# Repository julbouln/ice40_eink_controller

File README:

FPGA & STM32F0 driven EINK controller

- Final FPGA board: https://oshpark.com/shared_projects/rBoQ8bop
- The links on the Kitnic page make ordering the parts easier: https://kitnic.it/boards/github.com/julbouln/ice40_eink_controller/
- ifusb companion: https://github.com/julbouln/ifusb

Prototype:
- OLIMEX iCE40HX1K-EVB (https://www.olimex.com/Products/FPGA/iCE40/iCE40HX1K-EVB/open-source-hardware)
- NUCLEO-F042K6 (http://www.st.com/content/st_com/en/products/evaluation-tools/product-evaluation-tools/mcu-eval-tools/stm32-mcu-eval-tools/stm32-mcu-nucleo/nucleo-f042k6.html)
- TPS65185EVM (http://www.ti.com/tool/tps65185evm)
- ED060SC7 Kindle 3 EINK screen (http://www.ebay.com/sch/i.html?_from=R40&_trksid=m570.l1313&_nkw=ED060SC7&_sacat=0)
- custom EINK connector board (https://oshpark.com/shared_projects/I7bqOkZB)

Project tree:
- controller/ EINK controller verilog icestorm project
- hardware/ custom ice40 + ED060SC7 connector board
- utils/ misc utilities, including dumper for various reverse engineered waveform file formats
- utils/ifusb/ ifusb host driver

References:
- http://essentialscrap.com/eink/
- http://www.eevblog.com/forum/microcontrollers/interfacing-epd-%28e-ink%29-display-from-kindle-anyone-tried/

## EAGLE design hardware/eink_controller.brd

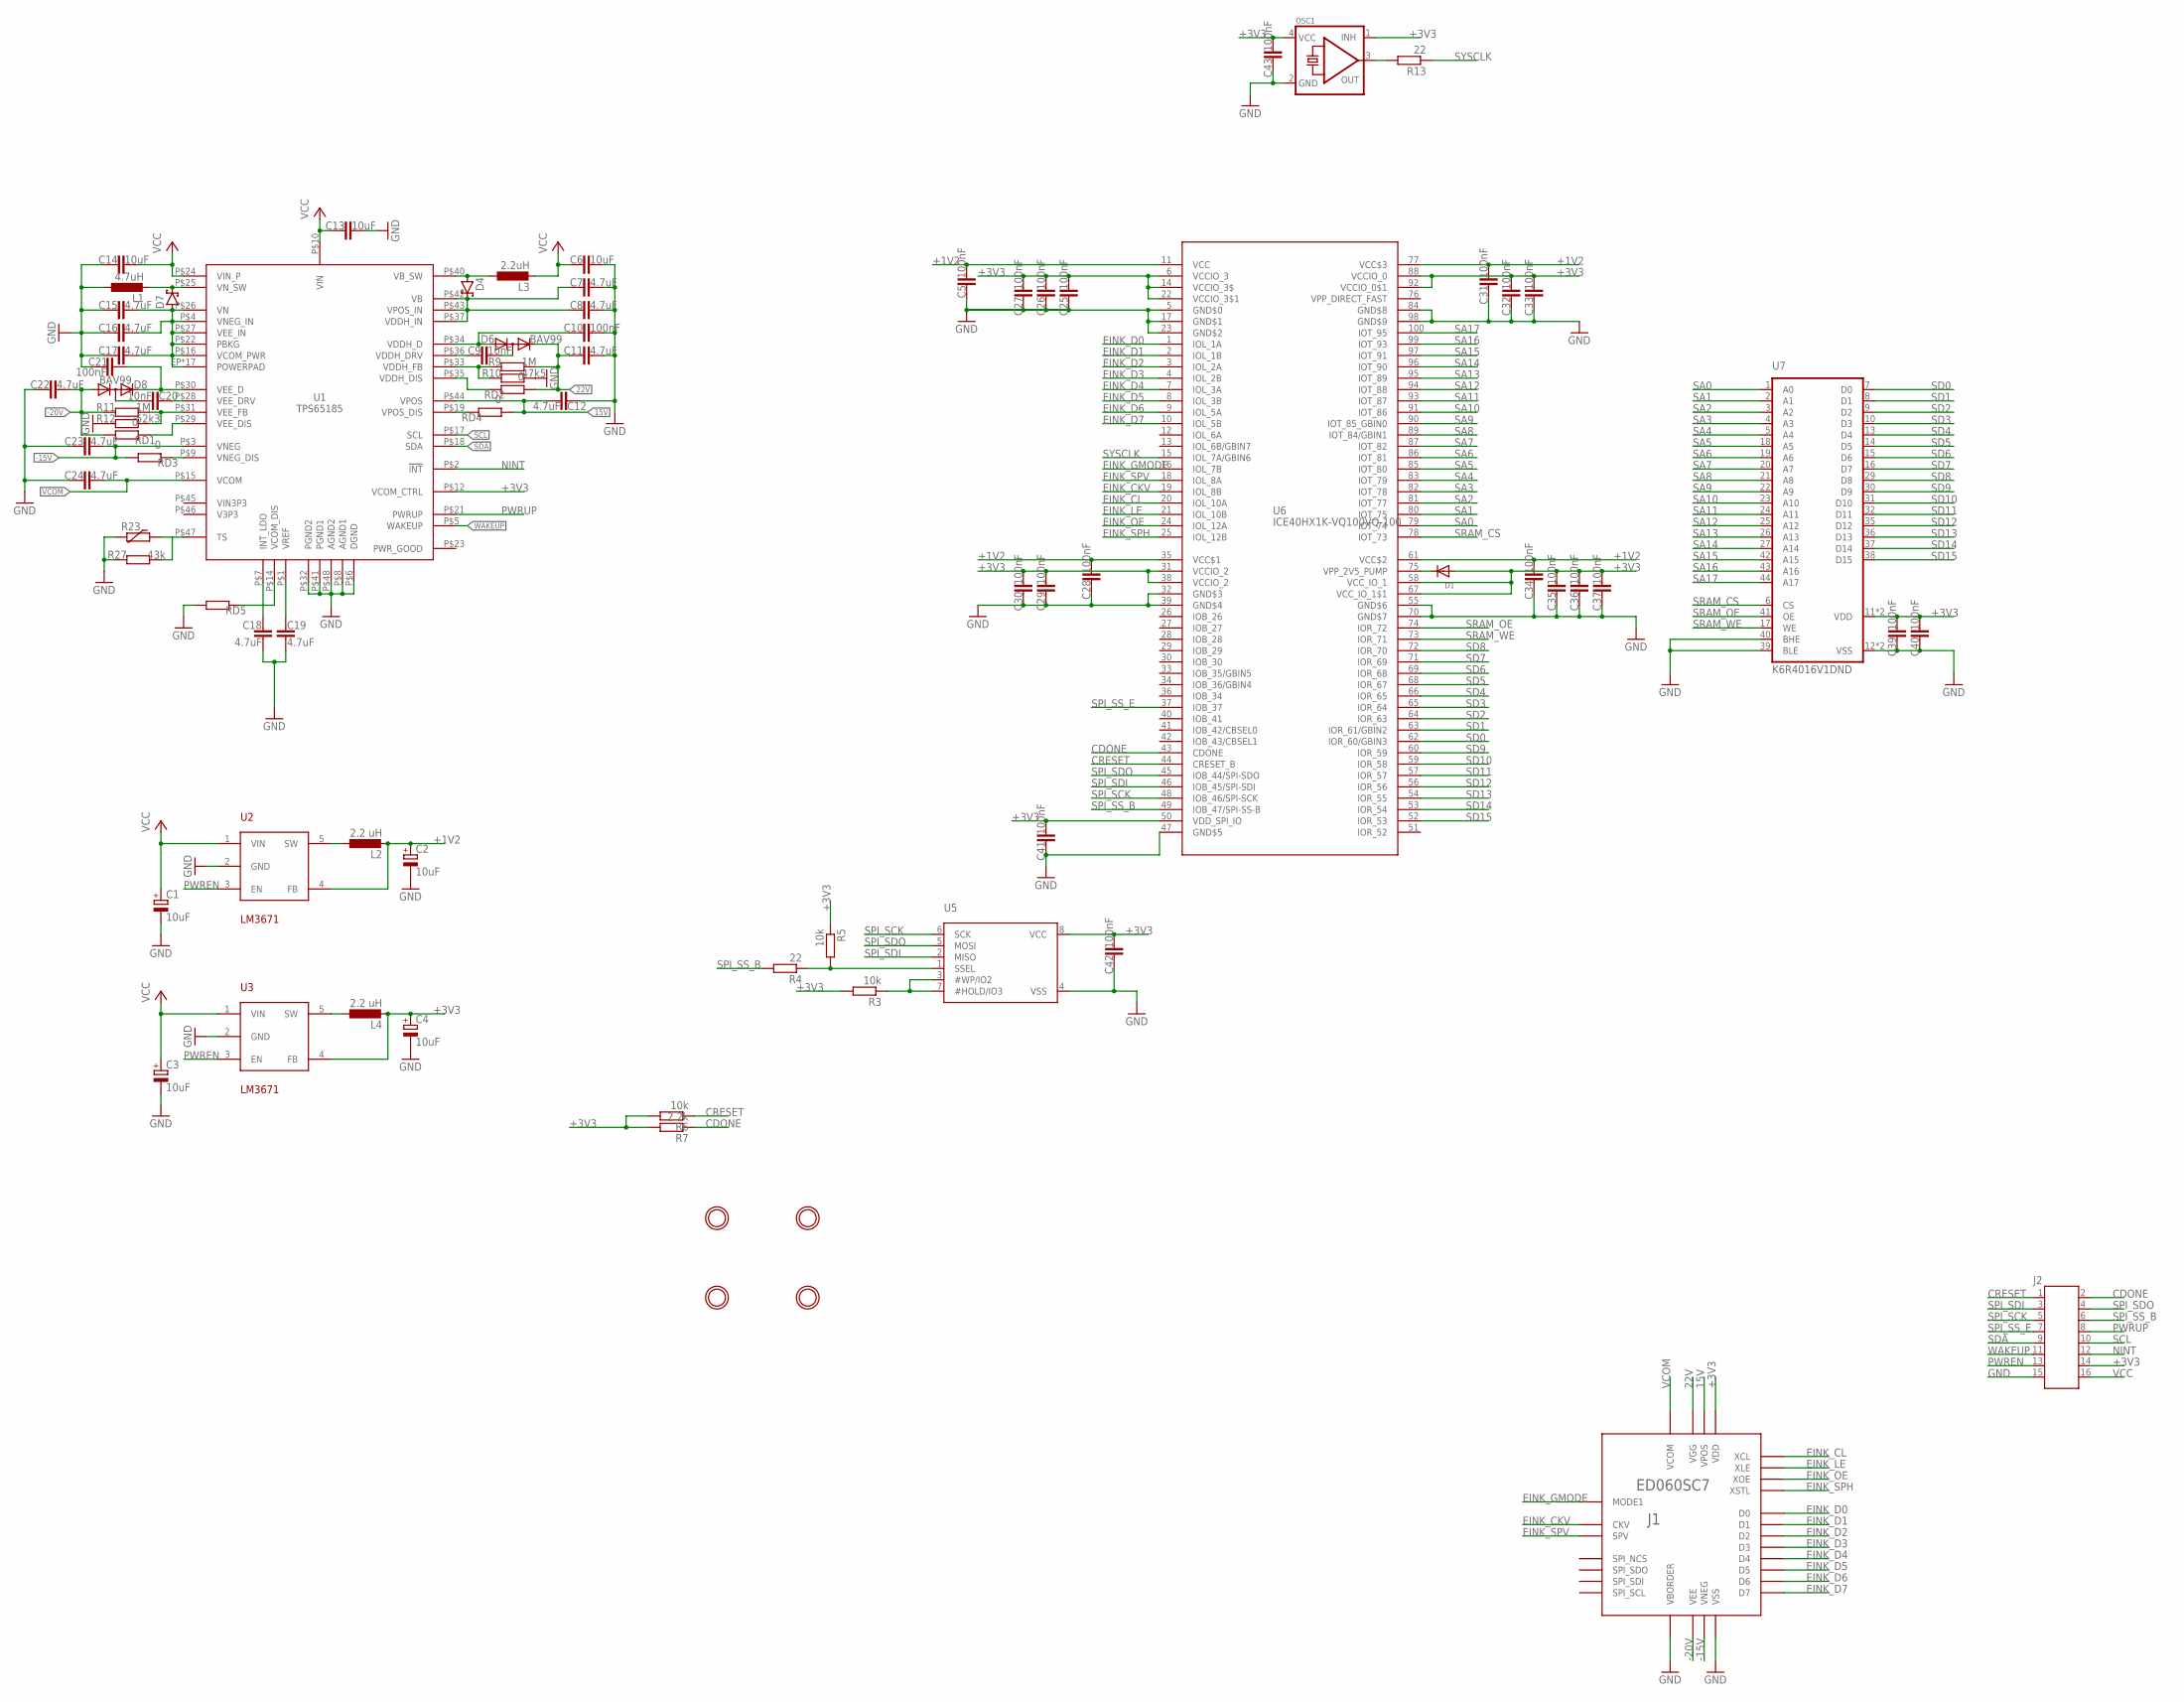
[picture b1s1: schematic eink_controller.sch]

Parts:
C1, C2, C3, C4: 10uF; A/3216-18R
C5, C10, C21, C25, C26, C27, C28, C29, C30, C31, C32, C33, C34, C35, C36, C37, C39, C40, C41, C42, C43: 100nF; C0603K
C6, C13, C14: 10uF; C0805K
C7, C8, C12, C15, C16, C17, C18, C19, C23, C24: 4.7uF; C0805K
C9, C20: 10nF; C0603K
C11, C22: 4.7uF; C0603K
D1: DIODESOD-123; SOD-123
D4, D7: MBR130T3G; SOD123
D6, D8: BAV99; SOT23
J1: ED060SC7; AXT334124
J2: 610116249221
L1: 4.7uH; L2825P
L2, L4: 2.2 uH; L2825P
L3: 2.2uH; L2825P
OSC1: OSCILLATOR; OSC_7X5MM
R3, R5, R6: 10k; R0603
R4, R13: 22; R0603
R7: 2.2k; R0603
R9, R11: 1M; R0603
R10: 47k5; R0603
R12: 52k3; R0603
R23: R-EU_R0603; R0603
R27: 43k; R0603
RD1, RD2, RD3, RD4: 0; R0603
RD5: R-EU_R0603; R0603
U1: TPS65185; VQFN48
U2, U3: LM3671; SOT23-5
U5: SPIFLASH_SOIC8208MIL; SOIC8_208MIL
U6: ICE40HX1K-VQ100VQ-100; TQFP100
U7: K6R4016V1DND; TSOP44-II
U$1, U$2, U$3, U$4: MOUNTINGHOLE2.0; MOUNTINGHOLE_2.0_PLATED

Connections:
15V: C12.2, J1.P$2 (VPOS), J1.P$4 (VPOS), RD4.1, U1.P$44 (VPOS)
22V: C11.1, D6.2 (C), J1.P$25 (VGG), R9.2, RD2.1
+1V2: C2.+, C5.2, C28.2, C31.2, C34.2, L2.2, U2.4 (FB), U6.11 (VCC), U6.35 (VCC$1), U6.61 (VCC$2), U6.77 (VCC$3)
+3V3: C4.+, C25.2, C26.2, C27.2, C29.2, C30.2, C32.2, C33.2, C35.2, C36.2, C37.2, C39.2, C40.2, C41.2, C42.2, C43.2, D1.A, J1.P$5 (VDD), J1.P$7 (VDD), J2.14, L4.2, OSC1.1 (INH), OSC1.4 (VCC), R3.2, R5.1, R6.2, R7.2, U1.P$12 (VCOM_CTRL), U3.4 (FB), U5.8 (VCC), U6.6 (VCCIO_3), U6.14 (VCCIO_3$), U6.22 (VCCIO_3$1), U6.31 (VCCIO_2), U6.38 (VCCIO_2), U6.50 (VDD_SPI_IO), U6.58 (VCC_IO_1), U6.67 (VCC_IO_1$1), U6.88 (VCCIO_0), U6.92 (VCCIO_0$1), U7.11 (VDD), U7.33 (VDD)
-15V: C23.2, J1.P$1 (VNEG), J1.P$3 (VNEG), RD3.2, U1.P$3 (VNEG)
-20V: C22.2, D8.1 (A), J1.P$27 (VEE), J1.P$29 (VEE), R11.1, RD1.2
CDONE: J2.2, R7.1, U6.43 (CDONE)
CRESET: J2.1, R6.1, U6.44 (CRESET_B)
EINK_CKV: J1.P$28 (CKV), U6.19 (IOL_8B)
EINK_CL: J1.P$9 (XCL), U6.20 (IOL_10A)
EINK_D0: J1.P$13 (D0), U6.1 (IOL_1A)
EINK_D1: J1.P$14 (D1), U6.2 (IOL_1B)
EINK_D2: J1.P$15 (D2), U6.3 (IOL_2A)
EINK_D3: J1.P$16 (D3), U6.4 (IOL_2B)
EINK_D4: J1.P$17 (D4), U6.7 (IOL_3A)
EINK_D5: J1.P$18 (D5), U6.8 (IOL_3B)
EINK_D6: J1.P$19 (D6), U6.9 (IOL_5A)
EINK_D7: J1.P$20 (D7), U6.10 (IOL_5B)
EINK_GMODE: J1.P$26 (MODE1), U6.16 (IOL_7B)
EINK_LE: J1.P$10 (XLE), U6.21 (IOL_10B)
EINK_OE: J1.P$11 (XOE), U6.24 (IOL_12A)
EINK_SPH: J1.P$12 (XSTL), U6.25 (IOL_12B)
EINK_SPV: J1.P$30 (SPV), U6.18 (IOL_8A)
GND: C1.-, C2.-, C3.-, C4.-, C5.1, C6.2, C7.2, C8.2, C10.2, C11.2, C12.1, C13.2, C14.1, C15.1, C16.1, C17.1, C18.1, C19.1, C21.1, C22.1, C23.1, C24.1, C25.1, C26.1, C27.1, C28.1, C29.1, C30.1, C31.1, C32.1, C33.1, C34.1, C35.1, C36.1, C37.1, C39.1, C40.1, C41.1, C42.1, C43.1, J1.P$6 (VSS), J1.P$8 (VSS), J1.P$31 (VSS), J1.P$32 (VBORDER), J2.15, L1.1, OSC1.2 (GND), R10.2, R12.1, R23.1, R27.1, RD5.2, U1.P$6 (DGND), U1.P$8 (AGND1), U1.P$32 (PGND2), U1.P$41 (PGND1), U1.P$48 (AGND2), U2.2 (GND), U3.2 (GND), U5.4 (VSS), U6.5 (GND$0), U6.17 (GND$1), U6.23 (GND$2), U6.32 (GND$3), U6.39 (GND$4), U6.47 (GND$5), U6.55 (GND$6), U6.70 (GND$7), U6.84 (GND$8), U6.98 (GND$9), U7.12 (VSS), U7.34 (VSS), U7.39 (BLE), U7.40 (BHE)
unnamed: RD5.1, U1.P$14 (VCOM_DIS)
unnamed: L4.1, U3.5 (SW)
unnamed: R3.1, U5.3 (#WP/IO2), U5.7 (#HOLD/IO3)
unnamed: OSC1.3 (OUT), R13.2
unnamed: D4.2 (A), L3.1, U1.P$40 (VB_SW)
unnamed: D1.C, U6.75 (VPP_2V5_PUMP)
unnamed: L2.1, U2.5 (SW)
unnamed: R4.1, R5.2, U5.1 (SSEL)
unnamed: C7.1, C8.1, D4.1 (C), U1.P$37 (VDDH_IN), U1.P$42 (VB), U1.P$43 (VPOS_IN)
unnamed: C10.1, D6.1 (A), U1.P$34 (VDDH_D)
unnamed: C9.1, U1.P$36 (VDDH_DRV)
unnamed: C9.2, D6.3 (AC)
unnamed: R9.1, R10.1, U1.P$33 (VDDH_FB)
unnamed: C20.2, D8.3 (AC)
unnamed: D7.1 (C), L1.2, U1.P$25 (VN_SW)
unnamed: C15.2, C16.2, C17.2, D7.2 (A), U1.EP (POWERPAD), U1.EP1 (POWERPAD), U1.EP2 (POWERPAD), U1.EP3 (POWERPAD), U1.EP4 (POWERPAD), U1.EP5 (POWERPAD), U1.EP6 (POWERPAD), U1.EP7 (POWERPAD), U1.EP8 (POWERPAD), U1.EP9 (POWERPAD), U1.EP10 (POWERPAD), U1.EP11 (POWERPAD), U1.EP12 (POWERPAD), U1.EP13 (POWERPAD), U1.EP14 (POWERPAD), U1.EP15 (POWERPAD), U1.EP16 (POWERPAD), U1.P$4 (VNEG_IN), U1.P$16 (VCOM_PWR), U1.P$22 (PBKG), U1.P$26 (VN), U1.P$27 (VEE_IN)
unnamed: C18.2, U1.P$7 (INT_LDO)
unnamed: C19.2, U1.P$1 (VREF)
unnamed: C21.2, D8.2 (C), U1.P$30 (VEE_D)
unnamed: RD3.1, U1.P$9 (VNEG_DIS)
unnamed: C20.1, U1.P$28 (VEE_DRV)
unnamed: R11.2, R12.2, U1.P$31 (VEE_FB)
unnamed: RD1.1, U1.P$29 (VEE_DIS)
unnamed: RD4.2, U1.P$19 (VPOS_DIS)
unnamed: RD2.2, U1.P$35 (VDDH_DIS)
unnamed: R23.2, R27.2, U1.P$47 (TS)
NINT: J2.12, U1.P$2 (!INT)
PWREN: J2.13, U2.3 (EN), U3.3 (EN)
PWRUP: J2.8, U1.P$21 (PWRUP)
SA0: U6.79 (IOT_74), U7.1 (A0)
SA1: U6.80 (IOT_75), U7.2 (A1)
SA2: U6.81 (IOT_77), U7.3 (A2)
SA3: U6.82 (IOT_78), U7.4 (A3)
SA4: U6.83 (IOT_79), U7.5 (A4)
SA5: U6.85 (IOT_80), U7.18 (A5)
SA6: U6.86 (IOT_81), U7.19 (A6)
SA7: U6.87 (IOT_82), U7.20 (A7)
SA8: U6.89 (IOT_84/GBIN1), U7.21 (A8)
SA9: U6.90 (IOT_85_GBIN0), U7.22 (A9)
SA10: U6.91 (IOT_86), U7.23 (A10)
SA11: U6.93 (IOT_87), U7.24 (A11)
SA12: U6.94 (IOT_88), U7.25 (A12)
SA13: U6.95 (IOT_89), U7.26 (A13)
SA14: U6.96 (IOT_90), U7.27 (A14)
SA15: U6.97 (IOT_91), U7.42 (A15)
SA16: U6.99 (IOT_93), U7.43 (A16)
SA17: U6.100 (IOT_95), U7.44 (A17)
SCL: J2.10, U1.P$17 (SCL)
SD0: U6.62 (IOR_60/GBIN3), U7.7 (D0)
SD1: U6.63 (IOR_61/GBIN2), U7.8 (D1)
SD2: U6.64 (IOR_63), U7.9 (D2)
SD3: U6.65 (IOR_64), U7.10 (D3)
SD4: U6.66 (IOR_65), U7.13 (D4)
SD5: U6.68 (IOR_67), U7.14 (D5)
SD6: U6.69 (IOR_68), U7.15 (D6)
SD7: U6.71 (IOR_69), U7.16 (D7)
SD8: U6.72 (IOR_70), U7.29 (D8)
SD9: U6.60 (IOR_59), U7.30 (D9)
SD10: U6.59 (IOR_58), U7.31 (D10)
SD11: U6.57 (IOR_57), U7.32 (D11)
SD12: U6.56 (IOR_56), U7.35 (D12)
SD13: U6.54 (IOR_55), U7.36 (D13)
SD14: U6.53 (IOR_54), U7.37 (D14)
SD15: U6.52 (IOR_53), U7.38 (D15)
SDA: J2.9, U1.P$18 (SDA)
SPI_SCK: J2.5, U5.6 (SCK), U6.48 (IOB_46/SPI-SCK)
SPI_SDI: J2.3, U5.2 (MISO), U6.46 (IOB_45/SPI-SDI)
SPI_SDO: J2.4, U5.5 (MOSI), U6.45 (IOB_44/SPI-SDO)
SPI_SS_B: J2.6, R4.2, U6.49 (IOB_47/SPI-SS-B)
SPI_SS_E: J2.7, U6.37 (IOB_37)
SRAM_CS: U6.78 (IOT_73), U7.6 (CS)
SRAM_OE: U6.74 (IOR_72), U7.41 (OE)
SRAM_WE: U6.73 (IOR_71), U7.17 (WE)
SYSCLK: R13.1, U6.15 (IOL_7A/GBIN6)
VCC: C1.+, C3.+, C6.1, C13.1, C14.2, J2.16, L3.2, U1.P$10 (VIN), U1.P$24 (VIN_P), U2.1 (VIN), U3.1 (VIN)
VCOM: C24.2, J1.P$21 (VCOM), J1.P$23 (VCOM), U1.P$15 (VCOM)
VPP_DIRECT_FAST: U6.76 (VPP_DIRECT_FAST)
WAKEUP: J2.11, U1.P$5 (WAKEUP)

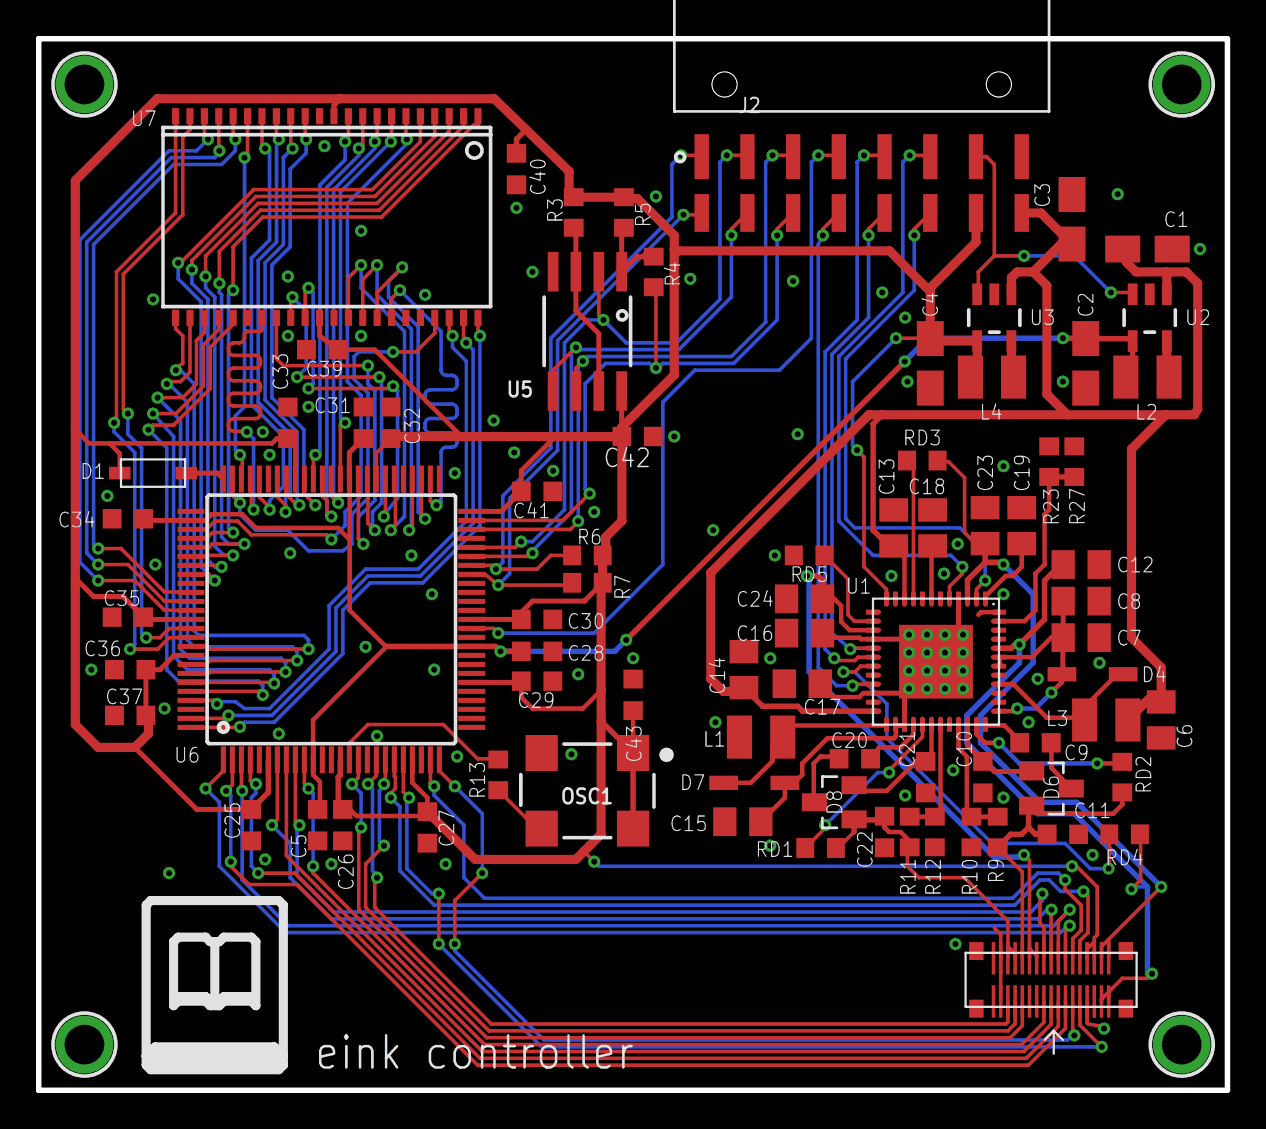
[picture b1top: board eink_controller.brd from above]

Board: 2 copper layers, 66.0 x 58.4 mm, 81 parts (0 on the bottom side), 101 nets.

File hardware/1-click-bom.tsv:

References	Qty	Description	Manufacturer	MPN	Manufacturer	MPN	Manufacturer	MPN	Manufacturer	MPN	Digikey	Mouser	RS	Newark	Farnell
C1, C2, C3, C4	4	10uF 3216-18	KEMET	B45196H2106K109	AVX	NOSA106M006R0800					NOSA106M006R0800-ND	581NOSA106M006R0800		58M9848	9751041
C11, C22	2	4.7uF 0603	Murata	GRM188R61A475KE15D	KEMET	C0603C475K8PACTU					490-10477-6-ND	80C0603C475K8P7867	6911155	14N2177	1572625
C5, C10, C21, C25, C26, C27, C28, C29, C30, C31, C32, C33, C34, C35, C36, C37, C39, C40, C41, C42, C43	21	100nF 0603	Yageo	CC0603KRX7R9BB104	Murata	GRM188R71H104KA93D	Samsung	CL10B104KB8NNNC			490-1519-6-ND	603CC603KRX7R9BB104	7235676	68R4788	8820023
C6, C13, C14	3	10uF 0805	Murata	GRM21BR61C106KE15L							490-3886-1-ND	81GRM21BR61C106KE15	7236039	35R0687	1762635
C7, C8, C12, C15, C16, C17, C18, C19, C23, C24	10	4.7uF 0805	Murata	GRM21BR61E475KA12L							490-3335-1-ND	81GRM21BR61E475KA12	7236057	24R6340	1735529
C9, C20	2	10nF 0603	Murata	GRM188R71H103KA01D	Yageo	CC0603KRX7R9BB103					490-1512-6-ND	81GRM39X103K50D	2040779	38K1669	1362418
D1	1	DIODE SOD-123	MCC	1N4148W-TP							1N4148WTPMSCT-ND	8331N4148WTP		51T5044	1924519
D4, D7	2	MBR130T3G SOD123	ON Semiconductor	MBR130T3G							MBR130T3GOSCT-ND	863MBR130T3G	7815635	42K0004	1611423
D6, D8	2	BAV99 SOT23	ON Semiconductor	BAV99LT1G							BAV99LT1GOSCT-ND	863BAV99LT1G	1249957	58M3990	9558667
J1	1	Socket (0.4mm pitch, 34-pin, Ni-barrie	Panasonic	AXT334124		ED060SC7					255-3300-1-ND	769AXT334124		29X3301	
J2	1	Wire-To-Board Connector, Surface Mount, Receptacle, 16 contacts, 2.54 mm	Würth Elektronik	610116249221							732-6082-1-ND	710610116249221			2470746
L1	1	4.7uH L-EUL2825P													
L2, L3, L4	3	2.2uH L-EUL2825P													
OSC1	1	100Mhz 7mm x 5mm	Ecliptek	EC2700TTS-100.000M TR	Ecliptek	EC2700ETTS-100.000M TR	Euroquartz	3EQHM57-ET-100.000R-C1.5						33P9351	1641083
R10	1	47k5 0603	Yageo	RC0603FR-0747K5L							311-47.5KHRCT-ND	603RC0603FR0747K5L		68R0096	1799346
R12	1	52k3 0603	Panasonic	ERA3ARB5232V	Yageo	RC0603FR-0752K3L	Vishay Dale	CRCW060352K3FKTA	Panasonic	ERA-3AEB5232V	ERA-3ARB5232V-ND	71CRCW060352.3K	7088940P	93T7397	2094621
R23, RD5, RD1, RD2, RD3, RD4	6	0 Ohm 0603	Vishay	CRCW06030000Z0EAHP	Vishay	CRCW06030000Z0EA	Panasonic	ERJ-3GEY0R00V			P0.0GCT-ND	667ERJ3GEY0R00V	8206736	65T8702	1469739
R27	1	43k 0603	Panasonic	ERA3APB433V							P43KAYDKR-ND	667ERA3APB433V			1892846
R3, R5, R6	3	10k 0603	Vishay	CRCW060310K0FKEA	Vishay	CRCW060310K0FKEAHP	Panasonic	ERJ-3EKF1002V			541-10.0KHDKR-ND	71CRCW060310KE3	8206742	61M5335	2303192
R4, R13	2	22R 0603	Yageo	RC0603JR-0722RL							311-22GRCT-ND	603RC0603JR0722RL		68R0168	1799407
R7	1	2.2k 0603	Panasonic	ERA3AEB222V							P2.2KDBDKR-ND	667ERA3AEB222V	566806P	01X1301	1577611
R9, R11	2	1M 0603	Vishay	CRCW06031M00FKEA	Yageo	RC0603FR-071ML	Vishay Dale	CRCW06031M00FKEAHP	Panasonic	ERJ-3EKF1004V	311-1.00MHRDKR-ND	667ERJ3EKF1004V	8206786	64R5311	1469746
U1	1	TPS65185RSLR	Texas Instruments	TPS65185RSLR	Texas Instruments	TPS65185SRGZR	Texas Instruments	TPS651851RSLT			296-29565-1-ND	595TPS651851RSLT		87X2294	
U2, U3	2		Texas Instruments	LM3671MF-3.3/NOPB							LM3671MF-3.3/NOPBDKR-ND	926LM3671MF3.3NOPB	7615876P	79K7839	2412057
U5	1	SPI FLASH SOIC8													
U6	1		Lattice Semiconductor	ICE40HX1K-VQ100							220-1567-ND	842ICE40HX1KVQ100	7720045P		2362850
U7	1	IS61WV2561	Samsung	K6R4016V1DND	ISSI	IS61WV25616BLL-10BLI-TR					IS61WV25616BLL-10BLI-TR-ND

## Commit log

2017-04-15 update readme & clean eink ifusb host
2017-04-16 cleanup + doc
2017-04-16 more doc
2017-04-17 add clipping + full speed
2017-04-17 test gif player
2017-04-17 misc
2017-04-17 add DU mode + fix wbf dump
2017-08-24 Make compatible with kitnic.it
2017-08-24 Improve retailer part selection a bit
2017-08-29 Fix BOM errors and improve part selection
2017-08-29 Add Kitnic link to README
2019-09-25 misc awaiting changes + use yosys 0.9 + nextpnr

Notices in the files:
parts and their libraries:
microbuilder: This work is placed in the public domain, and may be freely used for commercial and non-commercial work with the following conditions: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
Wurth_Elektronik_Electromechanic_Board_t: Copyright: Würth Elektronik
